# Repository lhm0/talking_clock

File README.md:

# Speaking Clock – Open Source Talking Clock for Visually Impaired Users

This repository is part of an open-source project for a simple, battery-powered **talking clock** designed for visually impaired and elderly users.

The device announces the current time at the press of a button.  
If the button is pressed a second time within a short time window, it also announces the date.

Watch the full project video on YouTube:  
[Talking Clock – Demo & Build](https://youtu.be/vuX4cK3g9_s?si=J2-5so-r-MG_IsnX)

## Part of an Accessible Devices Collection

This repository is part of a small collection of **minimalistic, accessibility-focused devices for visually impaired users**. All projects follow a similar philosophy: simple operation, tactile or acoustic feedback, and a strong focus on usability and low power consumption.

The currently available devices in this collection are:

- **[DAB+ Radio](https://github.com/lhm0/DAB_minimalist)** – A minimalist, easy-to-use DAB+ radio  
- **[Talking Clock](https://github.com/lhm0/talking_clock)** – This project: a clock that announces the time acoustically  
- **[Accessible IR Remote Control](https://github.com/lhm0/accessible_ir_remote)** – A tactile, low-power TV remote control  

All projects are designed to be practical, easy to reproduce, and suitable for everyday use by visually impaired users.

## Design Goals

The main design goals of this project are:

- A **minimal and accessible user interface**
- **Fully offline operation** (no internet required)
- **Very low power consumption** for multi-year battery life
- **Simple configuration** using a smartphone via Wi-Fi
- **Low-cost hardware** based on breakout modules and a custom PCB
- A **3D-printed enclosure** for easy assembly

The clock is based on an ESP32-S3 microcontroller, uses a DS3231 real-time clock for accurate timekeeping, and plays pre-generated MP3 audio files through an I2S audio amplifier and a small speaker.  
To achieve extremely low standby power consumption, the entire system is powered only when an announcement is made.

All hardware design files, firmware, and related resources are open source and can be adapted or extended for your own projects.

---

## Time Announcement Audio Files

This repository contains **English time announcement audio files (MP3)** generated for use in the speaking clock and similar applications, systems, or projects.

These files are used as building blocks to construct spoken time and date announcements, for example:

- “The time is noon”
- “It’s one p.m.”
- “Today is Monday”

---

## License / Usage

The audio files in this repository were generated using **ttsMP3.com**.  
According to the ttsMP3 FAQ, these MP3 files may be used in personal and commercial projects without restriction (see: https://ttsmp3.com/faq).

The audio files can therefore be:

- Used in personal projects  
- Used in commercial projects  
- Shared and redistributed as part of other projects  

**Note:** This repository does not include or distribute any TTS software or voices themselves, only the generated audio files.

---

## About

These audio files are intended to be used as building blocks for English time announcements in embedded projects such as the Speaking Clock.

If you use this repository, please make sure to check the current terms of ttsMP3.com to ensure compliance with their conditions.

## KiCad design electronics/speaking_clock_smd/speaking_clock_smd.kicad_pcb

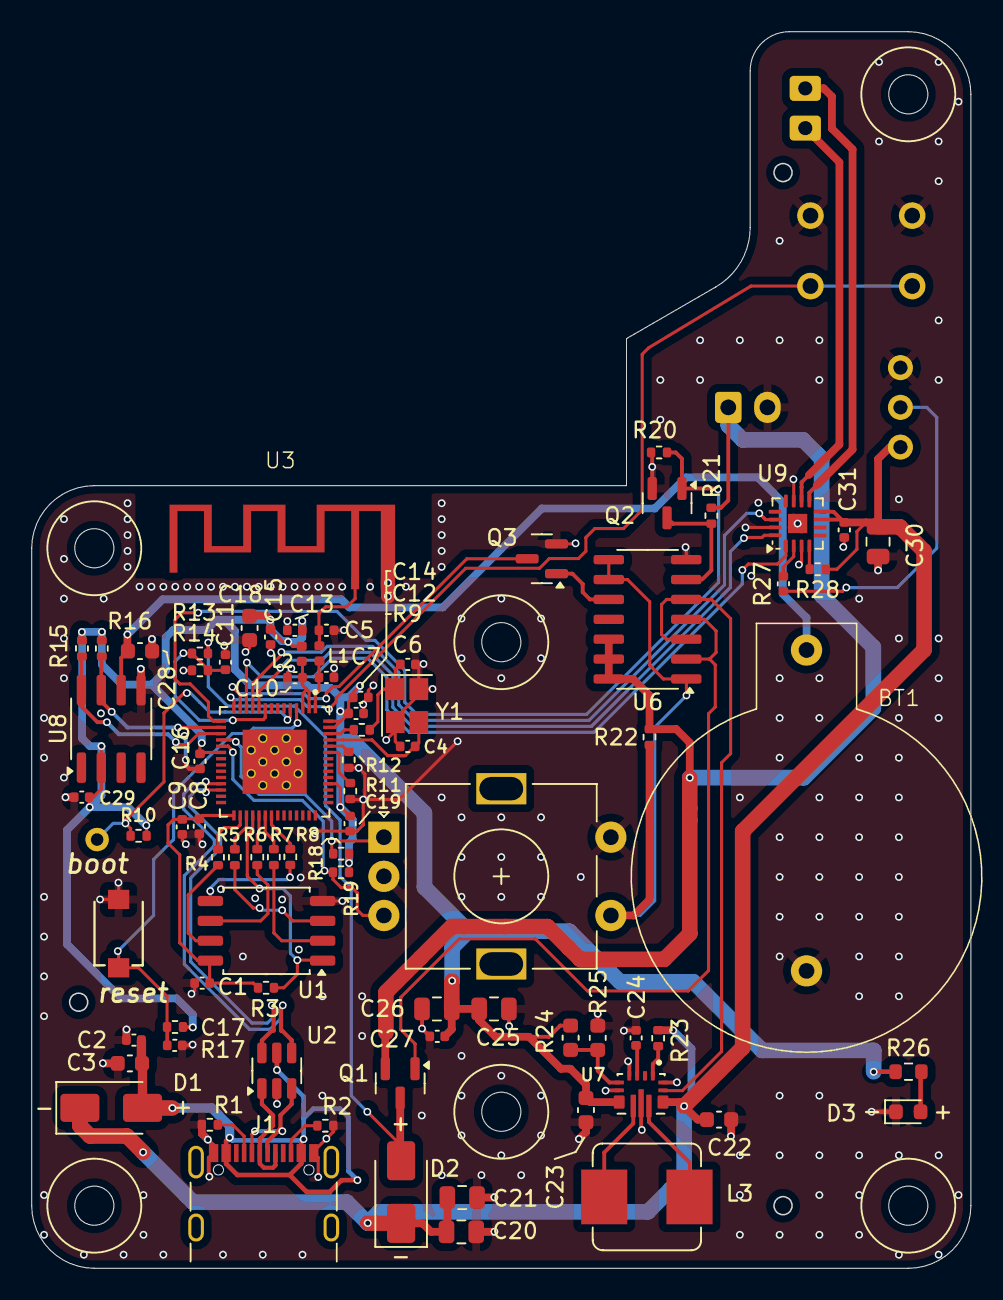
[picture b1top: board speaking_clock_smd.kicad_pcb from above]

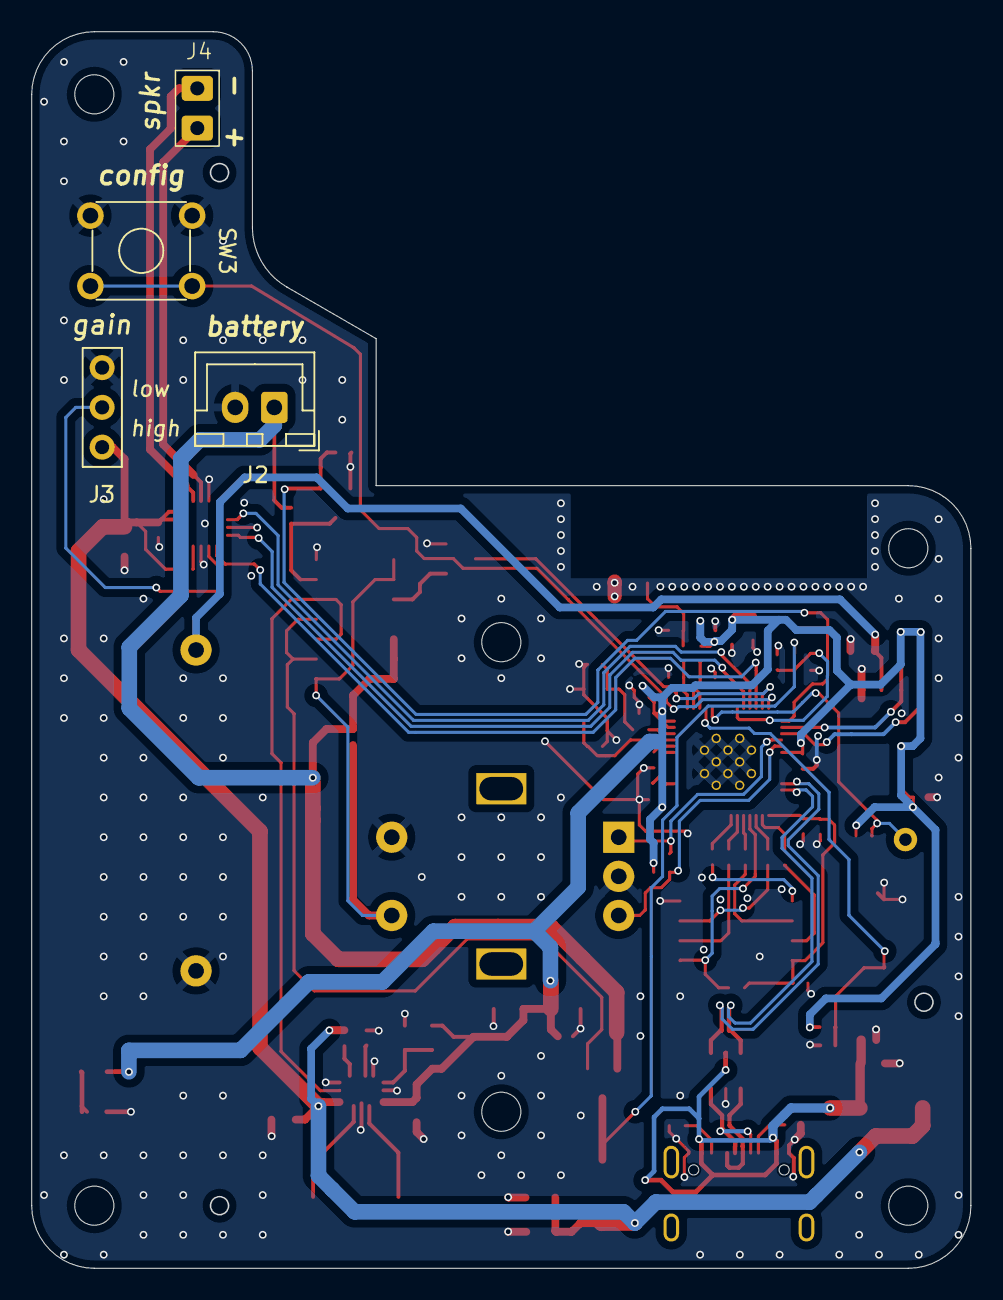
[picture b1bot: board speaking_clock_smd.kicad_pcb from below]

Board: 4 copper layers, 59.9 x 79.0 mm, 89 parts (4 on the bottom side), 62 nets.

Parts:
BT1: CR2032; Keytone_CR2032_holder
C1, C2, C8, C10, C11, C13, C16, C19, C24, C27, C29, C31: 100nF; C_0402_1005Metric
C3, C18, C22, C23: 10µF; C_0603_1608Metric
C4, C6: 10pF; C_0402_1005Metric
C5, C7: 3p3; C_0402_1005Metric
C9, C14, C15, C17: 1µF; C_0402_1005Metric
C12: 10nF; C_0402_1005Metric
C20, C21, C30: 10µF; C_0805_2012Metric
C25, C26: 22µF; C_0805_2012Metric
C28: 1nF; C_0603_1608Metric
D1, D2: SS24; D_SMA
D3: LED; LED_0603_1608Metric
J1: USB_C_Receptacle_USB2.0; USB_C_Receptacle
J2: Conn_01x02_Pin; JST_XH_B2B-XH-A_1x02_P2.50mm_Vertical
J3: Conn_01x03_Pin; 3_pin_jumper
J4: Conn_01x02_Pin; 2_pin
L1, L2: 2n2; L_0402_1005Metric
L3: 2.2µH; L_Bourns_SRP7028A_7.3x6.6mm
Q1: IRLML6401; SOT-23
Q2, Q3: AO3400A; SOT-23
R1, R2: 5k1; R_0402_1005Metric
R3, R20, R21, R22, R23, R28: 100k; R_0402_1005Metric
R4, R5, R6, R7, R8: 0; R_0402_1005Metric
R9: 22; R_0402_1005Metric
R10, R11, R12, R13, R17, R18, R19: 10k; R_0402_1005Metric
R14: 20k; R_0402_1005Metric
R15, R16: 4k7; R_0402_1005Metric
R24: 470k; C_0603_1608Metric
R25: 150k; C_0603_1608Metric
R26: 1k; R_0603_1608Metric
R27: 2k2; C_0402_1005Metric
SW1: reset; C720477
SW2: volume_knob; RotaryEncoder_Alps_EC11E-Switch_Vertical_H20mm
SW3: config; OmronTaster
U1: W25Q128JVS; SOIC-8_5.3x5.3mm_P1.27mm
U2: USBLC6-2SC6; SOT-23-6
U3: WiFi antenna; PCB_antenna
U4: ESP32-S3; IC_ESP32-S3
U5: 1pin
U6: HEF4093B; SOIC-14_3.9x8.7mm_P1.27mm
U7: TPS63070RNMR; VREG_TPS63070RNMR
U8: DS3231MZ; SOIC-8_3.9x4.9mm_P1.27mm
U9: MAX98357A; TQFN-16-1EP_3x3mm_P0.5mm_EP1.23x1.23mm
U20, U21, U22: JLC_tooling_hole
Y1: 40 MHz; Crystal_SMD_4Pin_3.2x2.5mm

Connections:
+3.3V: C12.1, C13.1, C14.1, C15.1, C16.1, C18.1, C19.1, C23.2, C25.1, C26.1, C27.1, C29.1, L2.2, R10.2, R15.2, R16.2, R17.1, R18.2, R19.1, R24.1, R26.1, U4.20 (VDD3P3_RTC), U4.46 (VDD3P3_CPU), U4.55 (VDDA1), U4.56 (VDDA2), U7.7_8 (VOUT), U8.2 (VCC)
/ESP32-S3 microcontroller/A5: J1.A5 (CC1), R1.1
/ESP32-S3 microcontroller/B5: J1.B5 (CC2), R2.1
/ESP32-S3 microcontroller/EN: C17.1, R17.2, SW1.1, U4.4 (CHIP_PU)
/ESP32-S3 microcontroller/ESP_D+: J1.A6 (D+), J1.B6 (D+), U2.1 (I/O1)
/ESP32-S3 microcontroller/ESP_D-: J1.A7 (D-), J1.B7 (D-), U2.3 (I/O2)
/ESP32-S3 microcontroller/GPIO4: C11.1, R13.2, R14.1, U4.9 (GPIO4)
/ESP32-S3 microcontroller/GPIO45: R11.1, U4.51 (GPIO45)
/ESP32-S3 microcontroller/GPIO46: R12.1, U4.52 (GPIO46)
/ESP32-S3 microcontroller/LNA: C7.1, L1.2, U4.1 (LNA_IN)
/ESP32-S3 microcontroller/SPICLK: R6.1, U1.6 (CLK)
/ESP32-S3 microcontroller/SPICLK_: R6.2, U4.33 (SPICLK)
/ESP32-S3 microcontroller/SPICS0: R3.1, U1.1 (~CS), U4.32 (SPICS0)
/ESP32-S3 microcontroller/SPID: R8.1, U1.5 (DI(IO0))
/ESP32-S3 microcontroller/SPID_: R8.2, U4.35 (SPID)
/ESP32-S3 microcontroller/SPIHD: R4.1, U1.7 (IO3)
/ESP32-S3 microcontroller/SPIHD_: R4.2, U4.30 (SPIHD)
/ESP32-S3 microcontroller/SPIQ: R7.1, U1.2 (DO(IO1))
/ESP32-S3 microcontroller/SPIQ_: R7.2, U4.34 (SPIQ)
/ESP32-S3 microcontroller/SPIWP: R5.1, U1.3 (IO2)
/ESP32-S3 microcontroller/SPIWP_: R5.2, U4.31 (SPIWP)
/ESP32-S3 microcontroller/UD_ESP+: U2.6 (I/O1), U4.26 (GPIO20)
/ESP32-S3 microcontroller/UD_ESP-: U2.4 (I/O2), U4.25 (GPIO19)
/ESP32-S3 microcontroller/VBUS3: C2.2, C3.1, D1.2 (A), J1.A4 (VBUS), J1.A9 (VBUS), J1.B4 (VBUS), J1.B9 (VBUS), U2.5 (VBUS)
/ESP32-S3 microcontroller/VDD3P3: C10.1, L2.1, U4.2 (VDD3P3), U4.3 (VDD3P3)
/ESP32-S3 microcontroller/VDD_SPI: C1.2, C8.1, C9.1, R3.2, U1.8 (VCC), U4.29 (VDD_SPI)
/ESP32-S3 microcontroller/XTAL_N: C4.1, U4.53 (XTAL_N), Y1.3
/ESP32-S3 microcontroller/XTAL_P: R9.2, U4.54 (XTAL_P)
/ESP32-S3 microcontroller/XTAL_Pp: C6.1, R9.1, Y1.1
/ESP32-S3 microcontroller/boot: R10.1, U4.5 (GPIO0), U5.1 (pin)
/ESP32-S3 microcontroller/feed: C5.1, L1.1, U3.2 (feed)
/peripherals/FB: R24.2, R25.1, U7.5 (FB)
/peripherals/Gain: R27.2, U9.2 (GAIN_SLOT)
/peripherals/Gain_Jumper: J3.2, R27.1
/peripherals/L1: L3.2, U7.11 (L1)
/peripherals/L2: L3.1, U7.9 (L2)
/peripherals/PS/SYNC: R23.2, U7.1 (PS/SYNC)
/peripherals/VAUX: C24.2, U7.3 (VAUX)
/peripherals/spkr_+: J4.2, U9.10 (OUTN)
/peripherals/spkr_-: J4.1, U9.9 (OUTP)
/peripherals//OFF: Q2.3 (D), R21.1, U6.6
/peripherals//ON: Q3.1 (G), U6.10
/peripherals//SD: R28.1, U9.4 (~SD_MODE)
GND: BT1.2 (-), C1.1, C2.1, C3.2, C4.2, C5.2, C6.2, C7.2, C8.2, C9.2, C10.2, C11.2, C12.2, C13.2, C14.2, C15.2, C16.2, C17.2, C18.2, C19.2, C20.2, C21.2, C22.1, C23.1, C24.1, C25.2, C26.2, C27.2, C28.1, C29.2, C30.2, C31.2, D3.1 (K), J1.A1 (GND), J1.A12 (GND), J1.B1 (GND), J1.B12 (GND), J2.2, J3.3, Q2.2 (S), Q3.2 (S), R1.2, R2.2, R11.2, R12.2, R14.2, R20.1, R25.2, SW1.2, SW2.C, SW2.S2, SW3.1 (A), U1.4 (GND), U2.2 (GND), U3.1 (GND), U4.57 (GND), U4.58 (GND), U4.59 (GND), U4.60 (GND), U4.61 (GND), U4.62 (GND), U4.63 (GND), U4.64 (GND), U4.65 (GND), U4.66 (GND), U4.67 (GND), U4.68 (GND), U4.69 (GND), U6.7 (GND), U7.4 (GND), U7.6 (FB2), U7.10 (PGND), U7.15 (VSEL), U8.5 (GND), U9.3 (GND), U9.11 (GND), U9.15 (GND), U9.17 (PAD), Y1.2, Y1.4
I2C_SCL: R15.1, U4.17 (GPIO12), U8.8 (SCL)
I2C_SDA: R16.1, U4.16 (GPIO11), U8.7 (SDA)
I2S_BCLK: U4.10 (GPIO5), U9.16 (BCLK)
I2S_DIN: U4.12 (GPIO7), U9.1 (DIN)
I2S_LRC: U4.11 (GPIO6), U9.14 (LRCLK)
unnamed: BT1.1 (+), C28.2, U8.6 (VBAT)
unnamed: D3.2 (A), R26.2
OFF: Q2.1 (G), R20.2, U4.15 (GPIO10)
ON: R22.1, SW2.S1, U6.1, U6.8, U6.9
VBat: J2.1, Q1.2 (S), R21.2, R22.2, U6.12, U6.13, U6.14 (VCC)
VBat_s: D2.2 (A), Q1.3 (D), R13.1
VIN: C20.1, C21.1, C22.2, C30.1, C31.1, D1.1 (K), D2.1 (K), J3.1, R23.1, R28.2, U7.12_13 (VIN), U9.7 (VDD), U9.8 (VDD)
config: SW3.2 (B), U4.14 (GPIO9)
enable: U6.3, U6.5, U7.14 (EN)
rotary_A: R18.1, SW2.A, U4.18 (GPIO13)
rotary_B: R19.2, SW2.B, U4.19 (GPIO14)
trigger: Q3.3 (D), U4.13 (GPIO8)
/enable: Q1.1 (G), U6.2, U6.4

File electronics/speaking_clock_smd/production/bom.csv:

Designator,Footprint,Quantity,Value,LCSC Part #
BT1,Keytone_CR2032_holder,1,CR2032,
"C1, C10, C11, C13, C16, C19, C2, C24, C27, C29, C31, C8",0402,12,100nF,C307331
C12,0402,1,10nF,C15195
"C14, C15, C17, C9",0402,4,1µF,C52923
"C18, C22, C23, C3",0603,4,10µF,C96446
"C20, C21, C30",0805,3,10µF,C15850
"C25, C26",0805,2,22µF,C45783
C28,0603,1,1nF,C1588
"C4, C6",0402,2,10pF,C32949
"C5, C7",0402,2,3p3,C1565
"D1, D2",D_SMA,2,SS24,C7420362
D3,0603,1,LED,C2286
J1,USB_C_Receptacle,1,USB_C_Receptacle_USB2.0,C709357
J2,JST_XH_B2B-XH-A_1x02_P2.50mm_Vertical,1,Conn_01x02_Pin,
J3,3_pin_jumper,1,Conn_01x03_Pin,
J4,2_pin,1,Conn_01x02_Pin,
"L1, L2",0402,2,2n2,C412264
L3,L_Bourns_SRP7028A_7.3x6.6mm,1,2.2µH,C167218
Q1,SOT-23,1,IRLML6401,C382329
"Q2, Q3",SOT-23,2,AO3400A,C20917
"R1, R2",0402,2,5k1,C25905
"R10, R11, R12, R13, R17, R18, R19",0402,7,10k,C25744
R14,0402,1,20k,C25765
"R15, R16",0402,2,4k7,C25900
"R20, R21, R22, R23, R28, R3",0402,6,100k,C25741
R24,0603,1,470k,C23178
R25,0603,1,150k,C22807
R26,0603,1,1k,C21190
R27,0402,1,2k2,C25879
"R4, R5, R6, R7, R8",0402,5,0,C17168
R9,0402,1,22,C25092
SW1,C720477,1,reset,C720477
SW2,RotaryEncoder_Alps_EC11E-Switch_Vertical_H20mm,1,volume_knob,
SW3,OmronTaster,1,config,
U1,SOIC-8_5.3x5.3mm_P1.27mm,1,W25Q128JVS,C97521
U2,SOT-23-6,1,USBLC6-2SC6,C2687116
"U20, U21, U22",JLC_tooling_hole,3,~,
U3,PCB_antenna,1,WiFi antenna,
U4,IC_ESP32-S3,1,ESP32-S3,C2913192
U5,1pin,1,~,
U6,SOIC-14_3.9x8.7mm_P1.27mm,1,HEF4093B,C7867
U7,VREG_TPS63070RNMR,1,TPS63070RNMR,C109322
U8,SOIC-8_3.9x4.9mm_P1.27mm,1,DS3231MZ,C107410
U9,TQFN-16-1EP_3x3mm_P0.5mm_EP1.23x1.23mm,1,MAX98357A,C910544
Y1,Crystal_SMD_4Pin_3.2x2.5mm,1,40 MHz,C379787

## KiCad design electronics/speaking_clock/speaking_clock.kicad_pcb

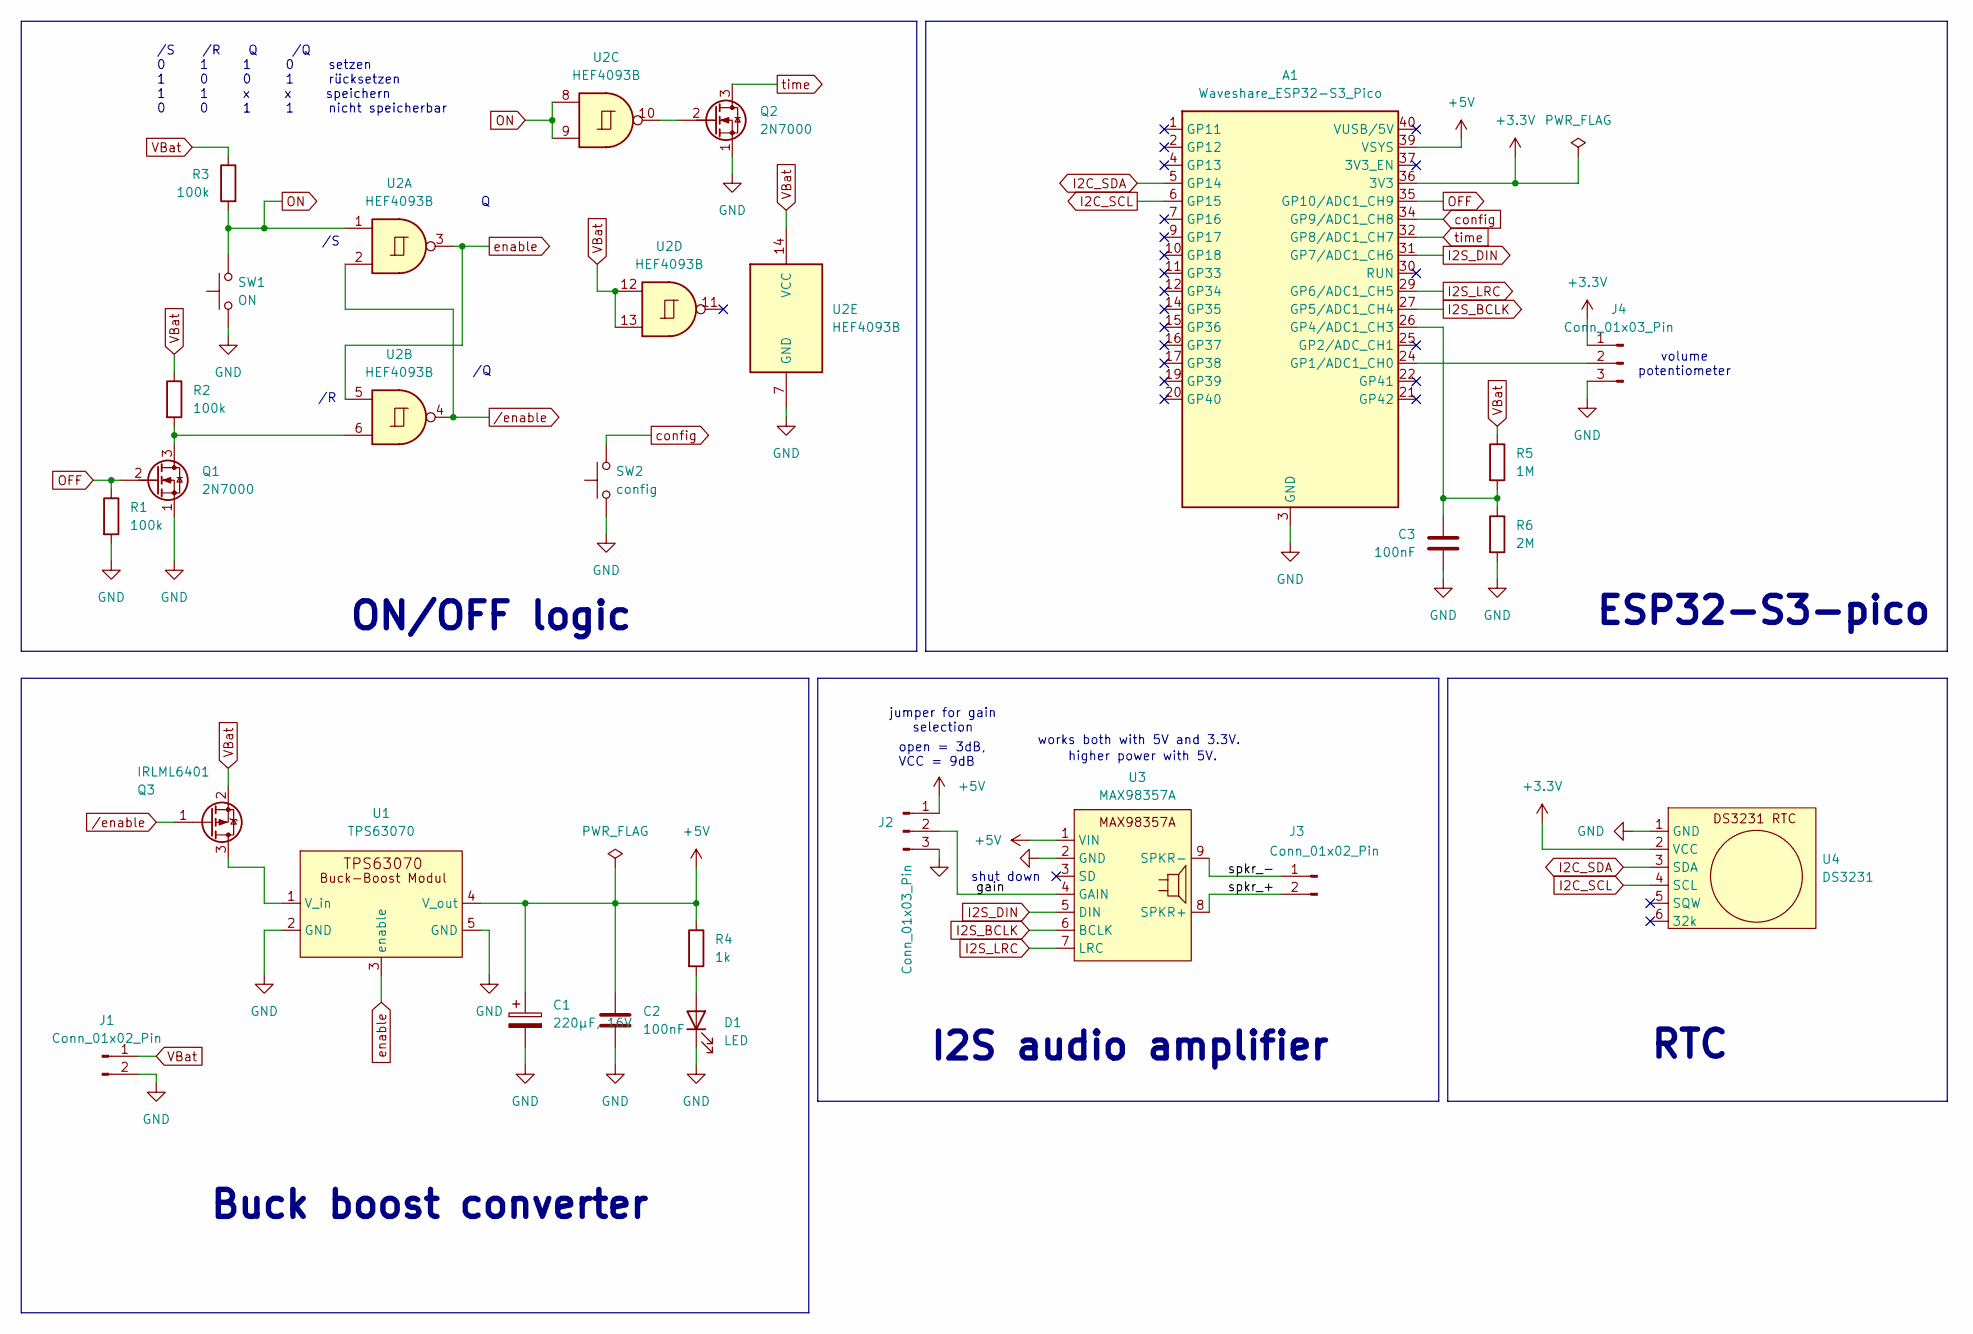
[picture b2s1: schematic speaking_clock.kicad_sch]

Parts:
A1: Waveshare_ESP32-S3_Pico; Waveshare_ESP32_S3_pico
C1: 220µF, 16V; CP_Radial_D6.3mm_P2.50mm
C2, C3: 100nF; C_Rect_L10.0mm_W2.5mm_P7.50mm_MKS4
D1: LED; LED_D3.0mm
J1: Conn_01x02_Pin; JST_XH_B2B-XH-A_1x02_P2.50mm_Vertical
J2, J4: Conn_01x03_Pin; 3_pin_jumper
J3: Conn_01x02_Pin; 2_pin
Q1, Q2: 2N7000; TO-92L_Inline
Q3: IRLML6401; SOT-23
R1, R2, R3: 100k; R_Axial_DIN0207_L6.3mm_D2.5mm_P10.16mm_Horizontal; LCSC C25768
R4: 1k; R_Axial_DIN0207_L6.3mm_D2.5mm_P10.16mm_Horizontal
R5: 1M; R_Axial_DIN0207_L6.3mm_D2.5mm_P10.16mm_Horizontal
R6: 2M; R_Axial_DIN0207_L6.3mm_D2.5mm_P10.16mm_Horizontal
SW1: ON; OmronTaster
SW2: config; OmronTaster
U1: TPS63070; TPS63070_breakout
U2: HEF4093B; DIP-14_W7.62mm
U3: MAX98357A; MAX98357A_breakout
U4: DS3231

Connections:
+3.3V: A1.36 (3V3), J4.1, U4.2 (VCC), U4.9 (VCC)
+5V: A1.39 (VSYS), C1.1, C2.1, J2.1, R4.1, U1.4 (V_out), U3.1 (VIN)
/gain: J2.2, U3.4 (GAIN)
/spkr_+: J3.2, U3.8 (SPKR+)
/spkr_-: J3.1, U3.9 (SPKR-)
GND: A1.3 (GND), A1.8 (GND), A1.13 (GND), A1.18 (GND), A1.23 (GND), A1.28 (GND), A1.33 (GND), A1.38 (GND), C1.2, C2.2, C3.2, D1.1 (K), J1.2, J2.3, J4.3, Q1.1 (S), Q2.1 (S), R1.2, R6.2, SW1.1 (A), SW2.1 (A), U1.2 (GND), U1.5 (GND), U2.7 (GND), U3.2 (GND), U4.1 (GND), U4.10 (GND)
I2C_SCL: A1.6 (GP15), U4.4 (SCL), U4.7 (SCL)
I2C_SDA: A1.5 (GP14), U4.3 (SDA), U4.8 (SDA)
I2S_BCLK: A1.27 (GP5/ADC1_CH4), U3.6 (BCLK)
I2S_DIN: A1.31 (GP7/ADC1_CH6), U3.5 (DIN)
I2S_LRC: A1.29 (GP6/ADC1_CH5), U3.7 (LRC)
unnamed: A1.24 (GP1/ADC1_CH0), J4.2
unnamed: A1.26 (GP4/ADC1_CH3), C3.1, R5.2, R6.1
unnamed: D1.2 (A), R4.2
unnamed: Q1.3 (D), R2.2, U2.6
unnamed: Q2.2 (G), U2.10
unnamed: Q3.3 (D), U1.1 (V_in)
OFF: A1.35 (GP10/ADC1_CH9), Q1.2 (G), R1.1
ON: R3.2, SW1.2 (B), U2.1, U2.8, U2.9
VBat: J1.1, Q3.2 (S), R2.1, R3.1, R5.1, U2.12, U2.13, U2.14 (VCC)
config: A1.34 (GP9/ADC1_CH8), SW2.2 (B)
enable: U1.3 (enable), U2.3, U2.5
time: A1.32 (GP8/ADC1_CH7), Q2.3 (D)
/enable: Q3.1 (G), U2.2, U2.4

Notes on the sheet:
/S /R Q /Q 0 1 1 0 setzen 1 0 0 1 rücksetzen 1 1 x x speichern 0 0 1 1 nicht speicherbar
open = 3dB, VCC = 9dB
I2S audio amplifier
ESP32-S3-pico
jumper for gain selection
works both with 5V and 3.3V.
RTC
higher power with 5V.
Buck boost converter
shut down
ON/OFF logic
volume potentiometer

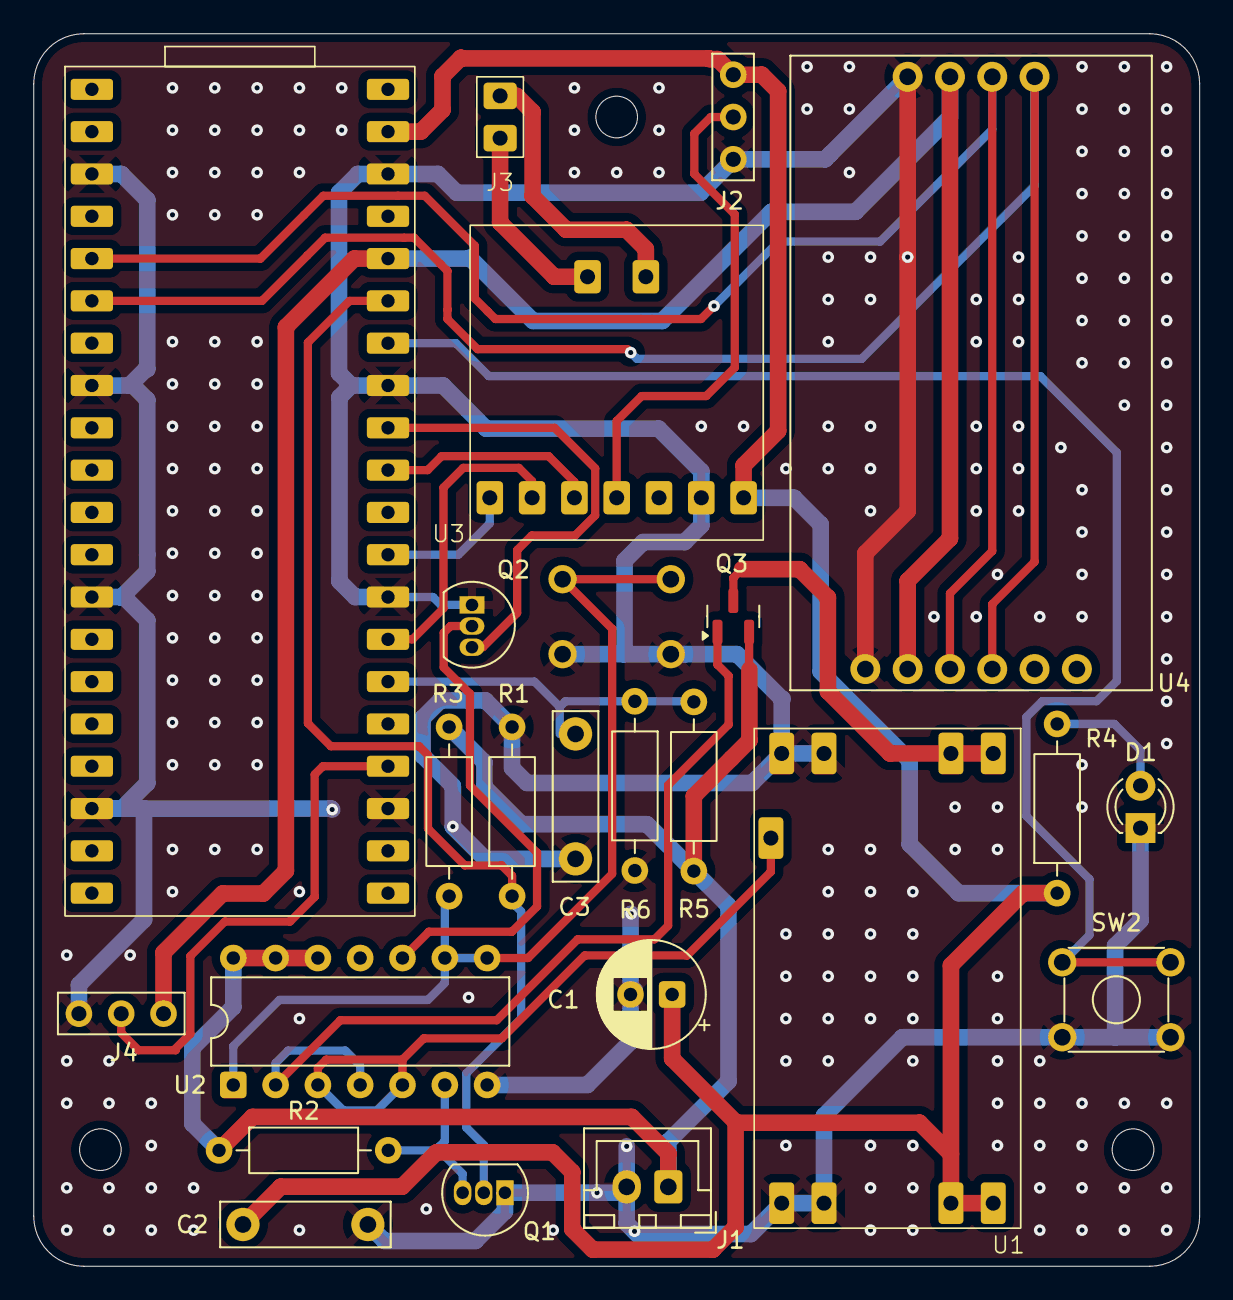
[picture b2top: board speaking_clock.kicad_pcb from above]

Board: 2 copper layers, 70.0 x 74.0 mm, 24 parts (1 on the bottom side), 24 nets.

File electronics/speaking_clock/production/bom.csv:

Designator,Footprint,Quantity,Value,LCSC Part #
A1,Waveshare_ESP32_S3_pico,1,Waveshare_ESP32-S3_Pico,
C1,CP_Radial_D6.3mm_P2.50mm,1,"220µF, 16V",
"C2, C3",C_Rect_L10.0mm_W2.5mm_P7.50mm_MKS4,2,100nF,
D1,LED_D3.0mm,1,LED,
J1,JST_XH_B2B-XH-A_1x02_P2.50mm_Vertical,1,Conn_01x02_Pin,
"J2, J4",3_pin_jumper,2,Conn_01x03_Pin,
J3,2_pin,1,Conn_01x02_Pin,
"Q1, Q2",TO-92L_Inline,2,2N7000,
Q3,SOT-23,1,IRLML6401,
"R1, R2, R3",R_Axial_DIN0207_L6.3mm_D2.5mm_P10.16mm_Horizontal,3,100k,C25768
R4,R_Axial_DIN0207_L6.3mm_D2.5mm_P10.16mm_Horizontal,1,1k,
R5,R_Axial_DIN0207_L6.3mm_D2.5mm_P10.16mm_Horizontal,1,1M,
R6,R_Axial_DIN0207_L6.3mm_D2.5mm_P10.16mm_Horizontal,1,2M,
SW1,OmronTaster,1,ON,
SW2,OmronTaster,1,config,
U1,TPS63070_breakout,1,TPS63070,
U2,DIP-14_W7.62mm,1,HEF4093B,
U3,MAX98357A_breakout,1,MAX98357A,
U4,DS3231,1,DS3231,

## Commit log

2026-02-17 Initial snapshot
2026-02-17 update pcb production data
2026-02-17 update STL files
2026-02-17 video link added to readme.md
2026-02-17 some photos added
2026-02-22 smd electronics added
2026-02-27 take over changes to electronics from test branch
